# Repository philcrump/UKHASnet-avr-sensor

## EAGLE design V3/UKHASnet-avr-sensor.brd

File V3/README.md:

Licensed under CC BY-SA 4.0

Copyright 2015 Phil Crump <phil@philcrump.co.uk>

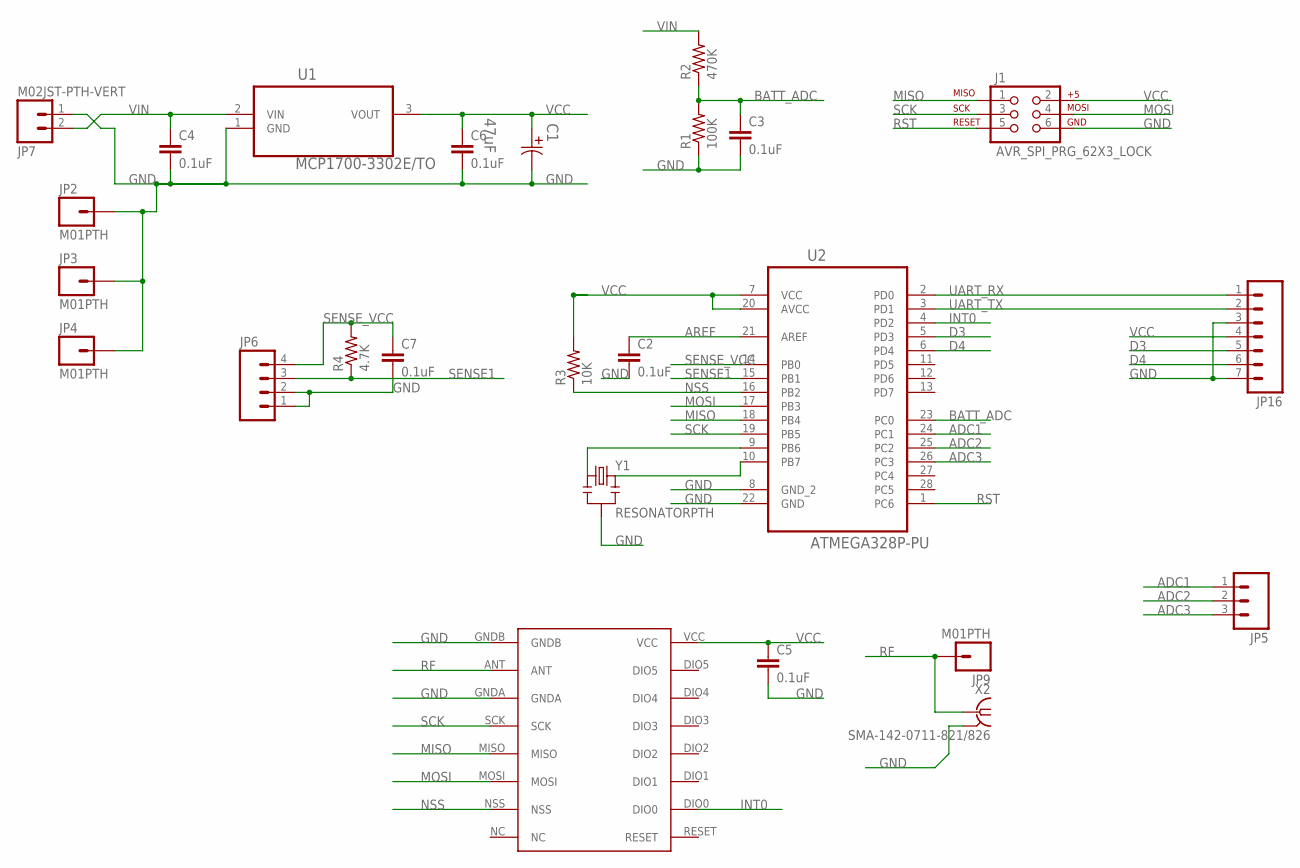
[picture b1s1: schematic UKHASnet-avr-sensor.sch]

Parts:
C1: 47uF; CAPPR150-400X1200
C2, C3, C4, C5, C6, C7: 0.1uF; C2.5-2
J1: AVR_SPI_PRG_62X3_LOCK; 2X3_LOCK
JP2, JP3, JP4, JP9: M01PTH; 1X01
JP5: M03PTH; 1X03
JP6: M04PTH; 1X04
JP7: M02JST-PTH-VERT; JST-2-PTH-VERT
JP16: M07; 1X07
R1: 100K; AXIAL-0.4
R2: 470K; AXIAL-0.4
R3: 10K; AXIAL-0.4
R4: 4.7K; AXIAL-0.4
U1: MCP1700-3302E/TO; TO127P254X495-3
U2: ATMEGA328P-PU; DIP254P762X457-28
U$1: RFM69HW; RFM
X2: SMA-142-0711-821/826; J502-ND-142-0711-821/826
Y1: RESONATORPTH; RESONATOR-PTH

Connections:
ADC1: JP5.1, U2.24 (PC1)
ADC2: JP5.2, U2.25 (PC2)
ADC3: JP5.3, U2.26 (PC3)
AREF: C2.1, U2.21 (AREF)
BATT_ADC: C3.1, R1.P$2 (2), R2.P$1 (1), U2.23 (PC0)
D3: JP16.5, U2.5 (PD3)
D4: JP16.6, U2.6 (PD4)
GND: C1.2, C2.2, C3.2, C4.2, C5.2, C6.2, C7.2, J1.6, JP2.1, JP3.1, JP4.1, JP6.1, JP6.2, JP7.1, JP16.3, JP16.7, R1.P$1 (1), U1.1 (GND), U2.8 (GND_2), U2.22 (GND), U$1.GNDA, U$1.GNDB, X2.G@1 (2), X2.G@2 (2), X2.G@3 (2), X2.G@4 (2), Y1.2
INT0: U2.4 (PD2), U$1.DIO0
MISO: J1.1, U2.18 (PB4), U$1.MISO
MOSI: J1.4, U2.17 (PB3), U$1.MOSI
unnamed: U2.10 (PB7), Y1.3
unnamed: U2.9 (PB6), Y1.1
NSS: R3.P$1 (1), U2.16 (PB2), U$1.NSS
RF: JP9.1, U$1.ANT, X2.1
RST: J1.5, U2.1 (PC6)
SCK: J1.3, U2.19 (PB5), U$1.SCK
SENSE1: JP6.3, R4.P$1 (1), U2.15 (PB1)
SENSE_VCC: C7.1, JP6.4, R4.P$2 (2), U2.14 (PB0)
UART_RX: JP16.1, U2.2 (PD0)
UART_TX: JP16.2, U2.3 (PD1)
VCC: C1.1, C5.1, C6.1, J1.2, JP16.4, R3.P$2 (2), U1.3 (VOUT), U2.7 (VCC), U2.20 (AVCC), U$1.VCC
VIN: C4.1, JP7.2, R2.P$2 (2), U1.2 (VIN)

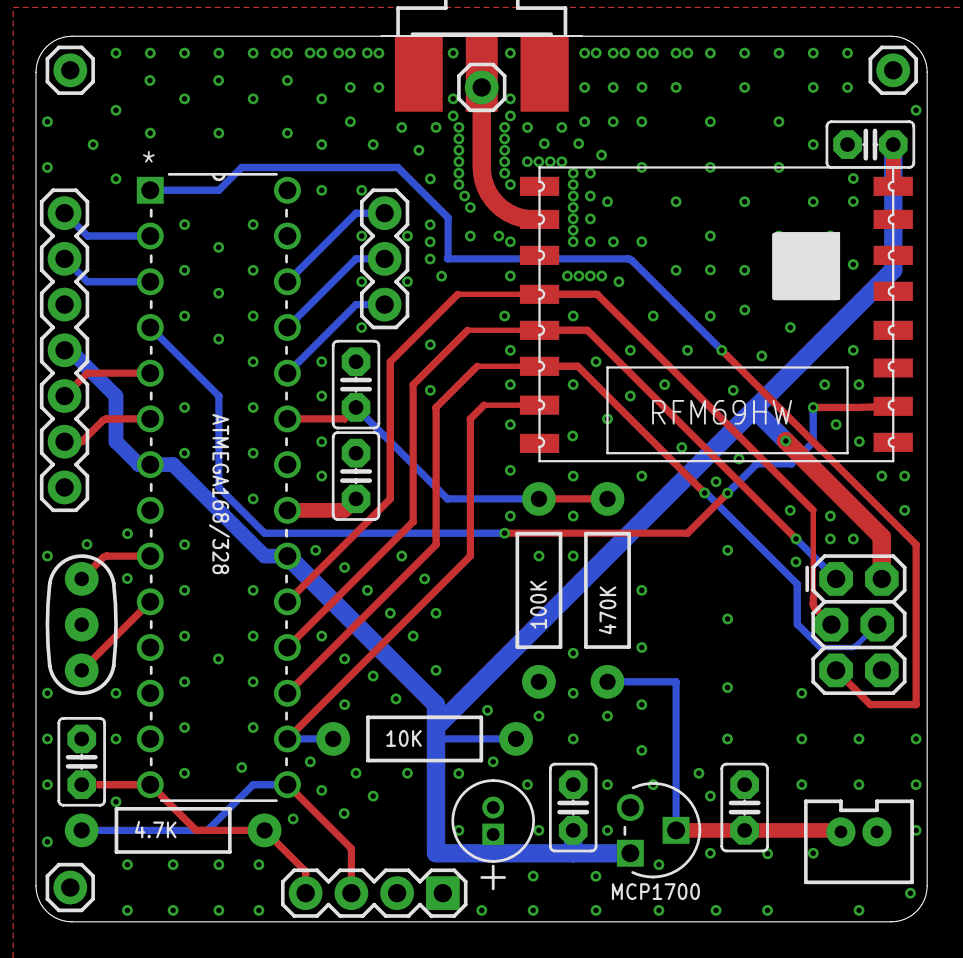
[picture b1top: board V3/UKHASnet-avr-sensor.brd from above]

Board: 2 copper layers, 49.5 x 49.2 mm, 25 parts (0 on the bottom side), 23 nets.

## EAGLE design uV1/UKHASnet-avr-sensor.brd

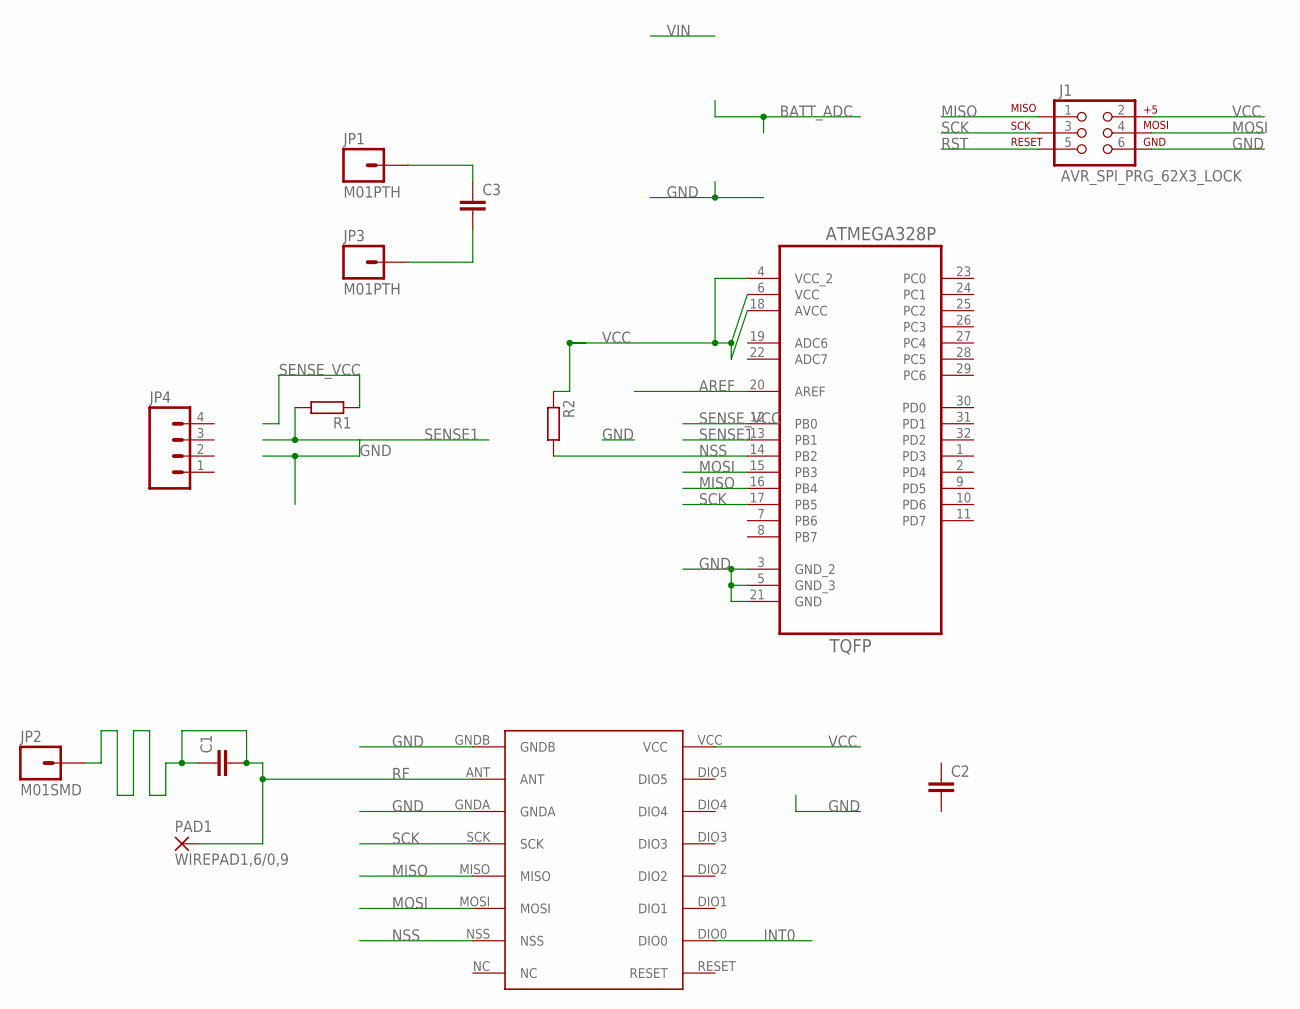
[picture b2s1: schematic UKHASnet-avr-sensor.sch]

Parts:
C1, C2, C3: C-EUC0402; C0402
J1: AVR_SPI_PRG_62X3_LOCK; 2X3_LOCK
JP1, JP3: M01PTH; 1X01
JP2: M01SMD; LUXEON-PAD
JP4: M04PTH; 1X04
PAD1: WIREPAD1,6/0,9; 1,6/0,9
R1, R2: R-EU_R0402; R0402
U2: ATMEGA328P-AU; QFP80P900X900X120-32N
U$1: RFM69HW; RFM

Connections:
AREF: U2.20 (AREF)
GND: C3.2, J1.6, JP3.1, U2.3 (GND_2), U2.5 (GND_3), U2.21 (GND), U$1.GNDA, U$1.GNDB
INT0: U$1.DIO0
MISO: J1.1, U2.16 (PB4), U$1.MISO
MOSI: J1.4, U2.15 (PB3), U$1.MOSI
NSS: R2.2, U2.14 (PB2), U$1.NSS
RF: C1.1, C1.2, JP2.P$1, PAD1.1, U$1.ANT
RST: J1.5
SCK: J1.3, U2.17 (PB5), U$1.SCK
SENSE1: R1.2, U2.13 (PB1)
SENSE_VCC: R1.1, U2.12 (PB0)
VCC: C3.1, J1.2, JP1.1, R2.1, U2.4 (VCC_2), U2.6 (VCC), U2.18 (AVCC), U$1.VCC

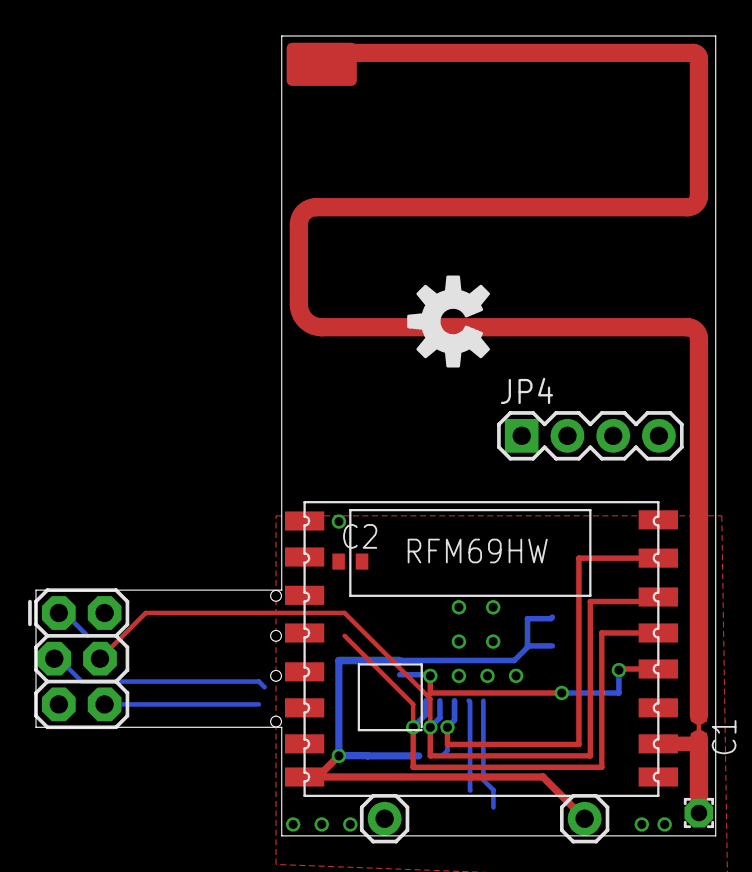
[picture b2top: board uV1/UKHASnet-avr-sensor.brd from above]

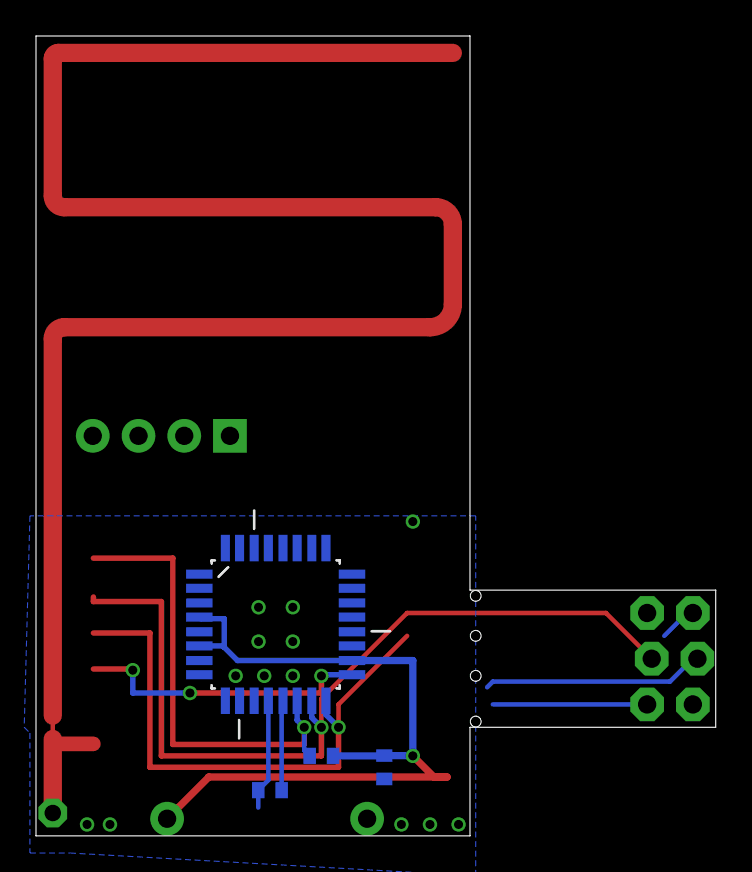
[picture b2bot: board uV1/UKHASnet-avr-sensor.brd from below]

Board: 2 copper layers, 37.8 x 44.4 mm, 14 parts (4 on the bottom side), 9 nets.

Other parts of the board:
U$3: OSHW-LOGO-M

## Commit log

2014-06-23 Initial setup
2014-06-24 Commit WIP Design Files
2014-06-24 Update for manufacture
2014-06-24 More little tweaks, send it off to Mitch!
2014-08-21 Clean up dir.
2014-08-22 Add V2 design files.
2014-08-22 Add V2 Schematic Render.
2014-08-22 Tweaks.
2014-08-22 Rerender schematic.
2014-08-22 Clean up DRC.
2014-08-22 Add gerblook board render.
2014-08-22 Add V2 BOM.
2014-08-22 Correct cap calue.
2014-08-22 Add resistor values.
2014-08-25 V2 Layout tweaks.
2014-08-25 V2: Reset view.
2014-08-25 Add sparkfun lib git submodule.
2014-08-25 Add OSHW logo.
2014-08-25 Update V2 Board render.
2014-08-25 V2 Tweaks.
2014-08-25 V2: All vias to round.
2014-08-25 v2: Update board render.
2014-08-27 Remove incorrect MCP1700 Order Code from BOM.
2014-10-05 Add extra pad for dht22.
2014-10-05 Add gerber runs.
2014-10-05 Add gedit backup files to gitignore.
2014-10-05 Fix dht22 pad.
2014-10-05 Rerender board.
2014-10-05 Silkscreen changes.
2014-10-05 Add gerbers.
2014-10-08 Drive sensor vcc from AVR PB0.
2014-10-08 Stitching.
2014-10-08 Schematic Aesthetics.
2014-10-08 Rerender schematic+board.
2014-10-13 Update BOM
2014-10-28 V2: Add to BOM.
2014-10-28 Add CAM files.
2014-11-10 Add V3.
2014-11-10 Adjust V3 Silkscreen.
2014-11-10 Line up labels with Pins
2014-11-10 Add final V3 files.
2014-11-10 Add ukhasnet logo layer to Gerbers.
2014-11-10 Add beginnings of micro sensor board.
2014-11-11 Clean up after eagle.
2014-11-11 Add V3 Render.
2014-11-11 Move GPIO headers to line up. (0.1")
2014-11-11 Increase groundplane isolation to 0.1"
2014-11-11 More silkscreen tweaks.
2014-11-12 Not much progress.
2014-11-21 Add V3 Schematic Render.
2014-12-01 Reduce Battery Voltage Resistor Divider Values.
2014-12-01 Add Layout render.
2014-12-21 Typo in BOM
2015-08-17 Tweak component placement, add vias, more silk labels.
2015-08-17 Add V3 r2 gerbers.

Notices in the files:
parts and their libraries:
SparkFun-Connectors: Licensing: CC v3.0 Share-Alike You are welcome to use this library for commercial purposes.
SparkFun-Aesthetics: Licensing: Creative Commons ShareAlike 4.0 International - https://creativecommons.org/licenses/by-sa/4.0
